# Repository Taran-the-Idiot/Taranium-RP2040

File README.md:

# Taranium-RP2040

An RP2040 devboard that is made to be compact and have its pins horizontally rather than vertically so it can have better packaging for my projects. Specifically this was made for my [driving macropad](https://github.com/Taran-the-Idiot/carpad) because the original microcontroller I was using did not have enough pins and all the alternatives took up a large amount of vertical space and would not package well

This board has the following features:

- USBc Port as USBc is superior
- 8MB Flash
- 25 pins
- 18 GPIO pins
- A Reset button

Anyways onwards to the next part

## Pinout

Here is the pinout diagram for this board.

There are 25 pins in total.

- 18 GPIO
- 3 GND
- 2 +5V(the VBUS label is a lie)(im sorry i didnt know what VBUS meant)
- 1 +3V3
- 1 RUN

## Schematic

Here is the schematic for the board.

## PCB

### PCB Top Side

### PCB Bottom Side

### Silkscreen

## Symbol/Footprint

A Kicad Symbol and Footprint for this board can be found in the [kicad](kicad/) folder.

Currently there is no plan to include footprints and symbols for other software.

## BOM

|Item|Source|Price($USD)|
|----|------|-----|
|PCB|JLCPCB|3.04|
|PCBa|JLCPCB|45.24|
|JLC Shipping|JLCPCB|1.5|
|Headers|[aliexpress](https://www.aliexpress.com/item/4000988113226.html?algo_pvid=bc2dc20b-ab48-4370-b92b-af39fdf054ba&algo_exp_id=bc2dc20b-ab48-4370-b92b-af39fdf054ba-6&pdp_ext_f=%7B%22order%22%3A%228387%22%2C%22eval%22%3A%221%22%2C%22fromPage%22%3A%22search%22%7D&pdp_npi=6%40dis%21AUD%211.84%211.39%21%21%211.31%210.99%21%4021033d9d17786630634743789ec4a9%2110000013202368848%21sea%21AU%210%21ABX%211%210%21n_tag%3A-29910%3Bd%3Ac34077ee%3Bm03_new_user%3A-29895%3BpisId%3A5000000203295501&curPageLogUid=Habg8k26UfcJ&utparam-url=scene%3Asearch%7Cquery_from%3A%7Cx_object_id%3A4000988113226%7C_p_origin_prod%3A)|1.6|
||Total|51.38|

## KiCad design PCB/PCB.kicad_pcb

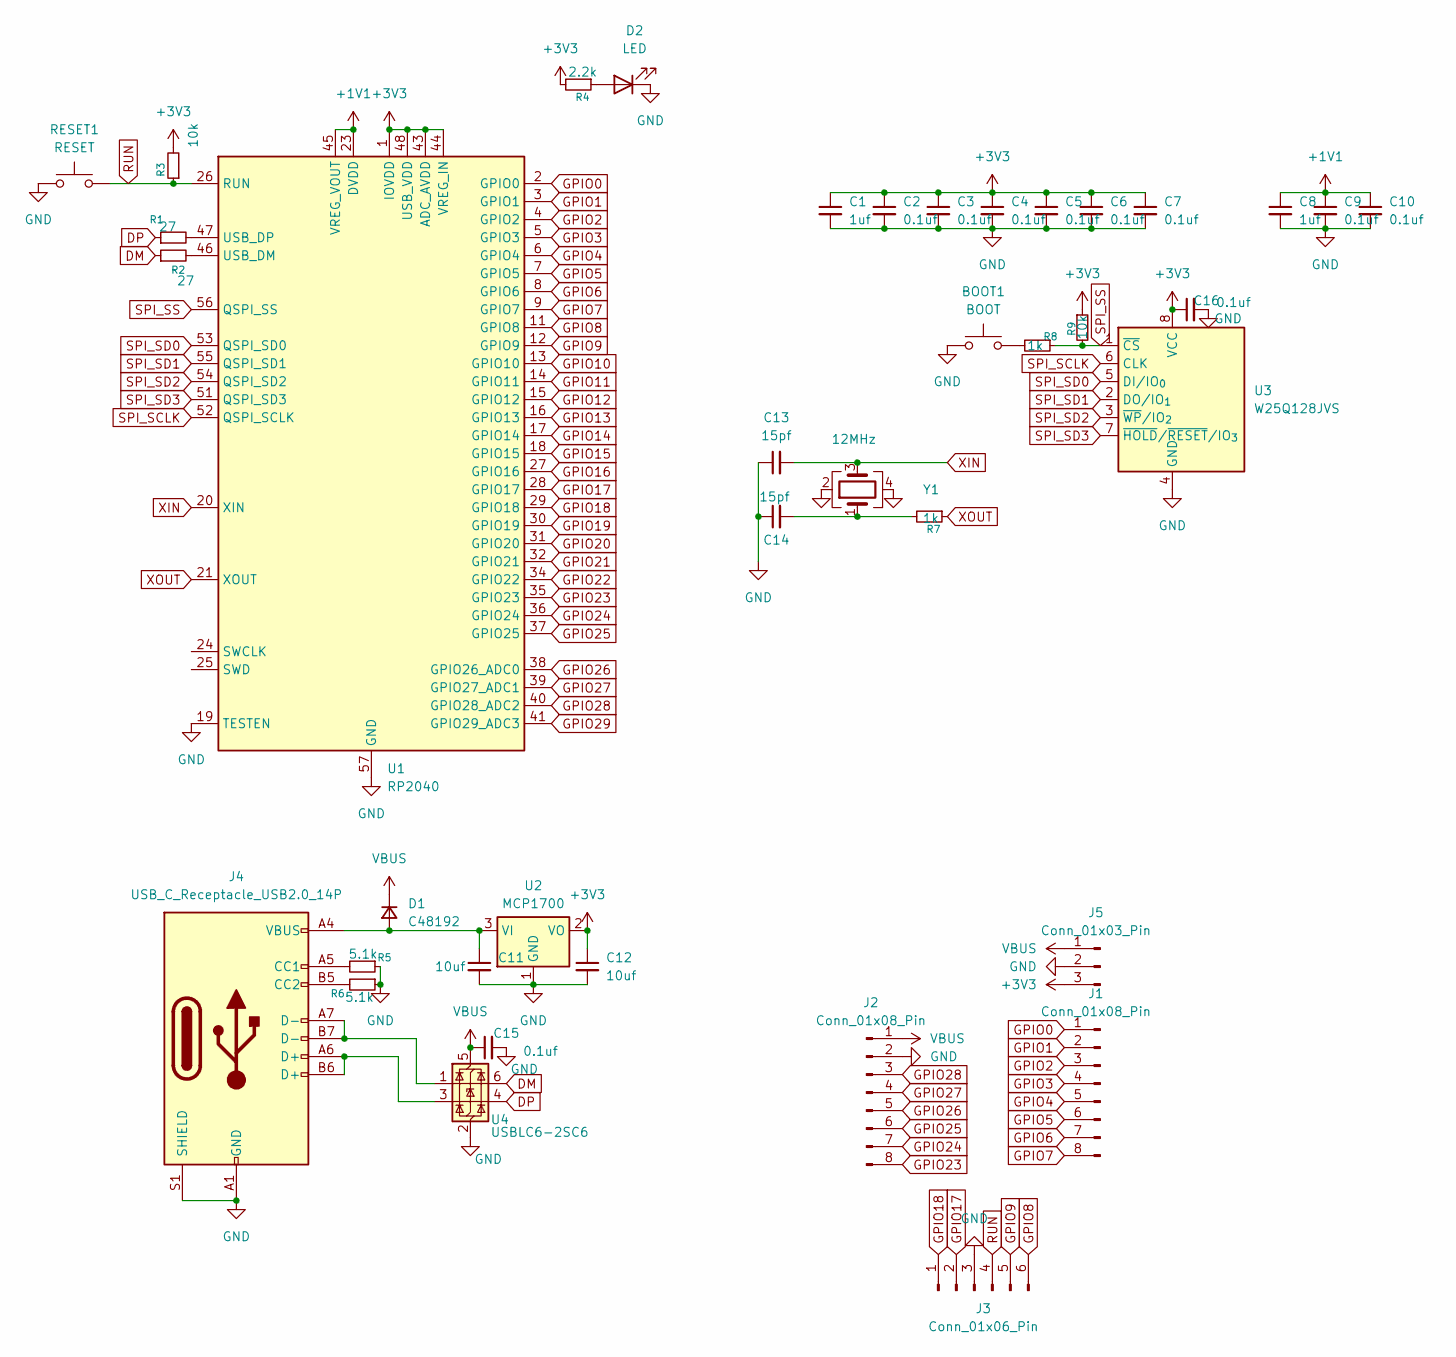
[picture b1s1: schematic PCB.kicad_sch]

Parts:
BOOT1: BOOT; C720477
C1, C8: 1uf; C_0402_1005Metric_Pad0.74x0.62mm_HandSolder
C2, C3, C4, C5, C6, C7, C9, C10, C15, C16: 0.1uf; C_0402_1005Metric_Pad0.74x0.62mm_HandSolder
C11, C12: 10uf; C_0603_1608Metric_Pad1.08x0.95mm_HandSolder
C13, C14: 15pf; C_0402_1005Metric_Pad0.74x0.62mm_HandSolder
D1: C48192; D_SOD-323_HandSoldering
D2: LED; LED_0805_2012Metric_Pad1.15x1.40mm_HandSolder
J1, J2: Conn_01x08_Pin; PinSocket_1x08_P2.54mm_Vertical
J3: Conn_01x06_Pin; PinSocket_1x06_P2.54mm_Vertical
J4: USB_C_Receptacle_USB2.0_14P; USB-C-SMD_20P-P0.50-L6.5-W8.9
J5: Conn_01x03_Pin; PinSocket_1x03_P2.54mm_Vertical
R1, R2: 27; R_0402_1005Metric_Pad0.72x0.64mm_HandSolder
R3, R9: 10k; R_0402_1005Metric_Pad0.72x0.64mm_HandSolder
R4: 2.2k; R_0402_1005Metric_Pad0.72x0.64mm_HandSolder
R5, R6: 5.1k; R_0402_1005Metric_Pad0.72x0.64mm_HandSolder
R7, R8: 1k; R_0402_1005Metric_Pad0.72x0.64mm_HandSolder
RESET1: RESET; C720477
U1: RP2040; QFN-56-1EP_7x7mm_P0.4mm_EP3.2x3.2mm
U2: MCP1700; SOT-23_Handsoldering
U3: W25Q128JVS; SOIC-8_5.3x5.3mm_P1.27mm
U4: USBLC6-2SC6; SOT-23-6
Y1: 12MHz; CRYSTAL-SMD_4P-L3.2-W2.5-BL

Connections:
+1V1: C8.1, C9.1, C10.1, U1.23 (DVDD), U1.45 (VREG_VOUT), U1.50 (DVDD)
+3V3: C1.1, C2.1, C3.1, C4.1, C5.1, C6.1, C7.1, C12.1, C16.1, J5.3, R3.2, R4.2, R9.1, U1.1 (IOVDD), U1.10 (IOVDD), U1.22 (IOVDD), U1.33 (IOVDD), U1.42 (IOVDD), U1.43 (ADC_AVDD), U1.44 (VREG_IN), U1.48 (USB_VDD), U1.49 (IOVDD), U2.2 (VO), U3.8 (VCC)
DM: R2.1, U4.6 (I/O1)
DP: R1.1, U4.4 (I/O2)
GND: BOOT1.1, C1.2, C2.2, C3.2, C4.2, C5.2, C6.2, C7.2, C8.2, C9.2, C10.2, C11.2, C12.2, C13.1, C14.1, C15.2, C16.2, D2.1 (K), J2.2, J3.3, J4.A1 (GND), J4.A12 (GND), J4.B1 (GND), J4.B12 (GND), J4.S1 (SHIELD), J5.2, R5.1, R6.1, RESET1.1, U1.19 (TESTEN), U1.57 (GND), U2.1 (GND), U3.4 (GND), U4.2 (GND), Y1.2, Y1.4
GPIO0: J1.1, U1.2 (GPIO0)
GPIO1: J1.2, U1.3 (GPIO1)
GPIO2: J1.3, U1.4 (GPIO2)
GPIO3: J1.4, U1.5 (GPIO3)
GPIO4: J1.5, U1.6 (GPIO4)
GPIO5: J1.6, U1.7 (GPIO5)
GPIO6: J1.7, U1.8 (GPIO6)
GPIO7: J1.8, U1.9 (GPIO7)
GPIO8: J3.6, U1.11 (GPIO8)
GPIO9: J3.5, U1.12 (GPIO9)
GPIO10: U1.13 (GPIO10)
GPIO11: U1.14 (GPIO11)
GPIO12: U1.15 (GPIO12)
GPIO13: U1.16 (GPIO13)
GPIO14: U1.17 (GPIO14)
GPIO15: U1.18 (GPIO15)
GPIO16: U1.27 (GPIO16)
GPIO17: J3.2, U1.28 (GPIO17)
GPIO18: J3.1, U1.29 (GPIO18)
GPIO19: U1.30 (GPIO19)
GPIO20: U1.31 (GPIO20)
GPIO21: U1.32 (GPIO21)
GPIO22: U1.34 (GPIO22)
GPIO23: J2.8, U1.35 (GPIO23)
GPIO24: J2.7, U1.36 (GPIO24)
GPIO25: J2.6, U1.37 (GPIO25)
GPIO26: J2.5, U1.38 (GPIO26_ADC0)
GPIO27: J2.4, U1.39 (GPIO27_ADC1)
GPIO28: J2.3, U1.40 (GPIO28_ADC2)
GPIO29: U1.41 (GPIO29_ADC3)
unnamed: BOOT1.2, R8.2
unnamed: C14.2, R7.2, Y1.1
unnamed: C11.1, D1.2 (A), J4.A4 (VBUS), J4.A9 (VBUS), J4.B4 (VBUS), J4.B9 (VBUS), U2.3 (VI)
unnamed: D2.2 (A), R4.1
unnamed: J4.A5 (CC1), R5.2
unnamed: J4.B5 (CC2), R6.2
unnamed: J4.A6 (D+), J4.B6 (D+), U4.3 (I/O2)
unnamed: J4.A7 (D-), J4.B7 (D-), U4.1 (I/O1)
unnamed: R2.2, U1.46 (USB_DM)
unnamed: R1.2, U1.47 (USB_DP)
RUN: J3.4, R3.1, RESET1.2, U1.26 (RUN)
SPI_SCLK: U1.52 (QSPI_SCLK), U3.6 (CLK)
SPI_SD0: U1.53 (QSPI_SD0), U3.5 (DI/IO_{0})
SPI_SD1: U1.55 (QSPI_SD1), U3.2 (DO/IO_{1})
SPI_SD2: U1.54 (QSPI_SD2), U3.3 (~WP/IO_{2})
SPI_SD3: U1.51 (QSPI_SD3), U3.7 (~HOLD/~RESET/IO_{3})
SPI_SS: R8.1, R9.2, U1.56 (QSPI_SS), U3.1 (~CS)
VBUS: C15.1, D1.1 (K), J2.1, J5.1, U4.5 (VBUS)
XIN: C13.2, U1.20 (XIN), Y1.3
XOUT: R7.1, U1.21 (XOUT)

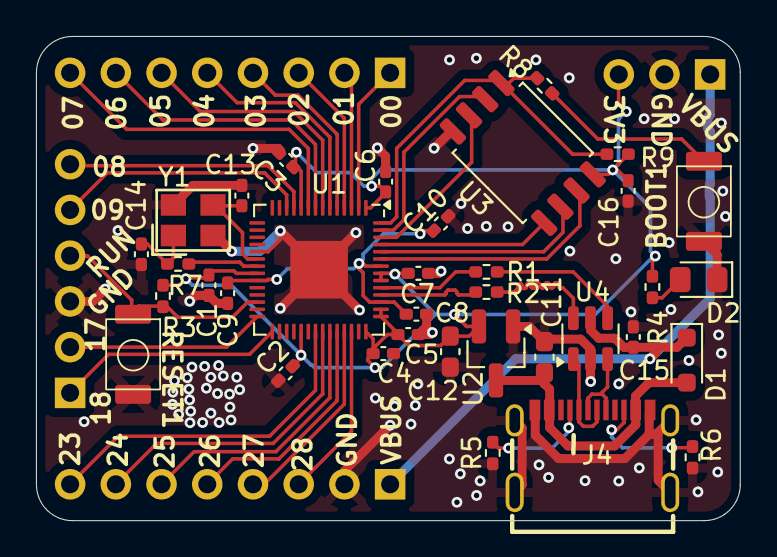
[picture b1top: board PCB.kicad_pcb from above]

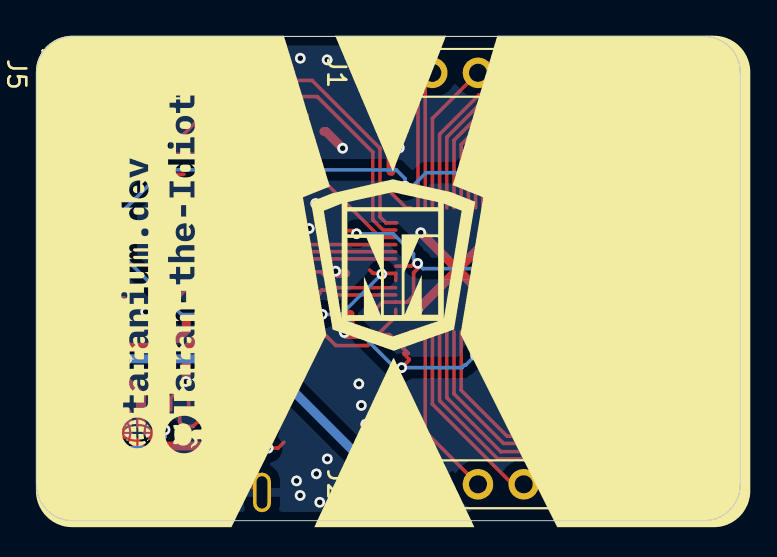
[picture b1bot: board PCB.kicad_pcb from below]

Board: 2 copper layers, 39.1 x 26.9 mm, 39 parts (4 on the bottom side), 43 nets.

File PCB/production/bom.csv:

Designator,Footprint,Quantity,Value,LCSC Part #
BOOT,C720477,1,BOOT,
"C1, C8",0402,2,1uf,
"C10, C15, C16, C2, C3, C4, C5, C6, C7, C9",0402,10,0.1uf,
"C11, C12",0603,2,10uf,
"C13, C14",0402,2,15pf,
D1,D_SOD-323_HandSoldering,1,C48192,
D2,0805,1,LED,
"J1, J2",PinHeader_1x08_P2.54mm_Vertical,2,Conn_01x07_Pin,
J3,PinHeader_1x06_P2.54mm_Vertical,1,Conn_01x06_Pin,
J4,USB-C-SMD_20P-P0.50-L6.5-W8.9,1,USB_C_Receptacle_USB2.0_14P,
J5,PinHeader_1x03_P2.54mm_Vertical,1,Conn_01x03_Pin,
"R1, R2",0402,2,27,
"R3, R9",0402,2,10k,
R4,0402,1,2.2,
"R5, R6",0402,2,22k,
"R7, R8",0402,2,1k,
RESET,C720477,1,RESET,
U1,QFN-56-1EP_7x7mm_P0.4mm_EP3.2x3.2mm,1,RP2040,
U2,SOT-23_Handsoldering,1,MCP1700,
U3,SOIC-8_5.3x5.3mm_P1.27mm,1,W25Q128JVS,
U4,SOT-23-6,1,USBLC6-2SC6,
Y1,CRYSTAL-SMD_4P-L3.2-W2.5-BL,1,12MHz,

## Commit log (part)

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2026-05-06 potato
2026-05-06 im gonna meta post nimit
2026-05-07 bleh
2026-05-09 havent commited in a while
2026-05-12 arson
2026-05-12 jounral
2026-05-12 more journal
2026-05-12 commit arson
2026-05-13 pinouts are cool
2026-05-13 production and stuff
2026-05-13 redme
2026-05-13 banana
2026-05-13 comit message
2026-05-13 jonal
